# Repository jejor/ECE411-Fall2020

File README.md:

# ECE411-Fall2020
Practicum Project: Safety Bar
Tiffani Shilts Hartman <tshilts2@pdx.edu>, Jennifer Jordan <jejor2@pdx.edu>, Katie Loseke <kloseke@pdx.edu>, Seth Rohrbach <rseth@pdx.edu>

## Executive Summary / Concept of Operations

This is a LED light bar system which will display power information from a distance of 300 feet. This system will be installed on a liquid fuel engine test stand and will display which sub-systems are receiving power and will display data on which individual valves are receiving power during the different engine firing stages. 

## Brief Market Analysis

This project can be adapted for a system with up to 9 inputs to display the power states of the lines. This is a safety and data sub-system for ensuring that all lines are powered as they should be within the purposes of the whole system. The Safety Bar would cost less than $200 if brought to market; this includes a rough estimate of component cost and assembly.

## Requirements

- Must be visible from 300 feet (91.5 meters).
- Must be able to take at least 9 power line (valve) inputs.
- Must be compatible with a 24V input to power the system.
- Should display all possible combinations of power states.
- Should cost less than $200 total.
- Should compare State Machine to the current valve states.
- Should have a battery backup with 1 hour of backup power.
- Should be protected from the elements within an enclosure.
- Should have thermal distribution system.
- May have data backup on the micro-controller.
- May be enclosed in an explosion proof box.
- May have rechargeable battery.

## System Architecture

#### The full system architecture for the Test Stand Automation & Regulation system with the Safety Bar sub-project (green circle):

#### Safety Bar Level 0 Block Diagram:

#### Safety Bar Level 1 Block Diagram:

## Design Specification

There are a total of 9 valves which states need to be compared to the software control state machine. This system will verify that the valves are responding to the software commands. To do this we will use sensors on each 9 valves, process the data on a micro-controller, compare the physical valve states to the expected valve states and display any relevant information to the user in the form of LED display codes. The LED bar will display the current state the system is in, if there is an error or if the physical state does not match the expected state, the LED bar will flash and display which valve is causing the error. 

- Sensor: Hall Effect
- Processor: STM32F0
- Actuator: LEDs
- Power: POE+ with backup battery

`Software Pseudocode:`

`LOOP:`

&nbsp;&nbsp;&nbsp;&nbsp; `READ: hall effect sensors`

&nbsp;&nbsp;&nbsp;&nbsp; `READ: STM32F0 state command`

&nbsp;&nbsp;&nbsp;&nbsp; `COMPARE: hall effect sensor data to state command`

&nbsp;&nbsp;&nbsp;&nbsp;&nbsp;&nbsp;&nbsp;&nbsp; `IF: doesn’t match`

&nbsp;&nbsp;&nbsp;&nbsp;&nbsp;&nbsp;&nbsp;&nbsp;&nbsp;&nbsp;&nbsp;&nbsp; `Sound Buzzer`

&nbsp;&nbsp;&nbsp;&nbsp;&nbsp;&nbsp;&nbsp;&nbsp;&nbsp;&nbsp;&nbsp;&nbsp; `Display binary value for which valve is causing the error`

&nbsp;&nbsp;&nbsp;&nbsp;&nbsp;&nbsp;&nbsp;&nbsp; `IF: does match`

&nbsp;&nbsp;&nbsp;&nbsp;&nbsp;&nbsp;&nbsp;&nbsp;&nbsp;&nbsp;&nbsp;&nbsp; `Display current state in binary`

&nbsp;&nbsp;&nbsp;&nbsp; `RECORD: data to SD card`

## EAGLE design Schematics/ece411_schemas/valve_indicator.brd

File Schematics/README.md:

# Eagle Schematics & Boards

## Valve Indicator

Purpose:
This board will collect valve position data using hall effect sensors mounted on nine solenoid valves and will report the current commanded state of the valves. 
The processor will compare the expected valve states with the currect reported valve states, 
if the states do not match the processor will output an indication over the LED arrays.
The LED arrays will display specific binary codes to indicate which valve does not match. 
If multiple valves do not match then the LED arrays will display all binary codes one after another based upon priority information.

Inputs:
- POE+ 24V Power
- UART Data
- Nine Hall Effect Sensors
- ST-Link V2 Emulator

Processor:
- STM32F042K

Outputs:
- Three LED Arrays
- One Buzzer
- SD Card Data Backup

### Libraries In Use

- Power Regulators: Diodes Inc. - AZ34063UMTR-G1.lbr
- Test Points: oresat-misc.lbr
- Processor: U-ST-STM32F042K-uC.lbr
- JTAG Emulator Connector: J-Samtec-FTSH-105-XXX-DV-K-ARM-SWD.lbr
- Diode: On Semiconductor - 1N5819G.lbr

### Design Rules

We are using the OshPark design rules for a 2-layer board.

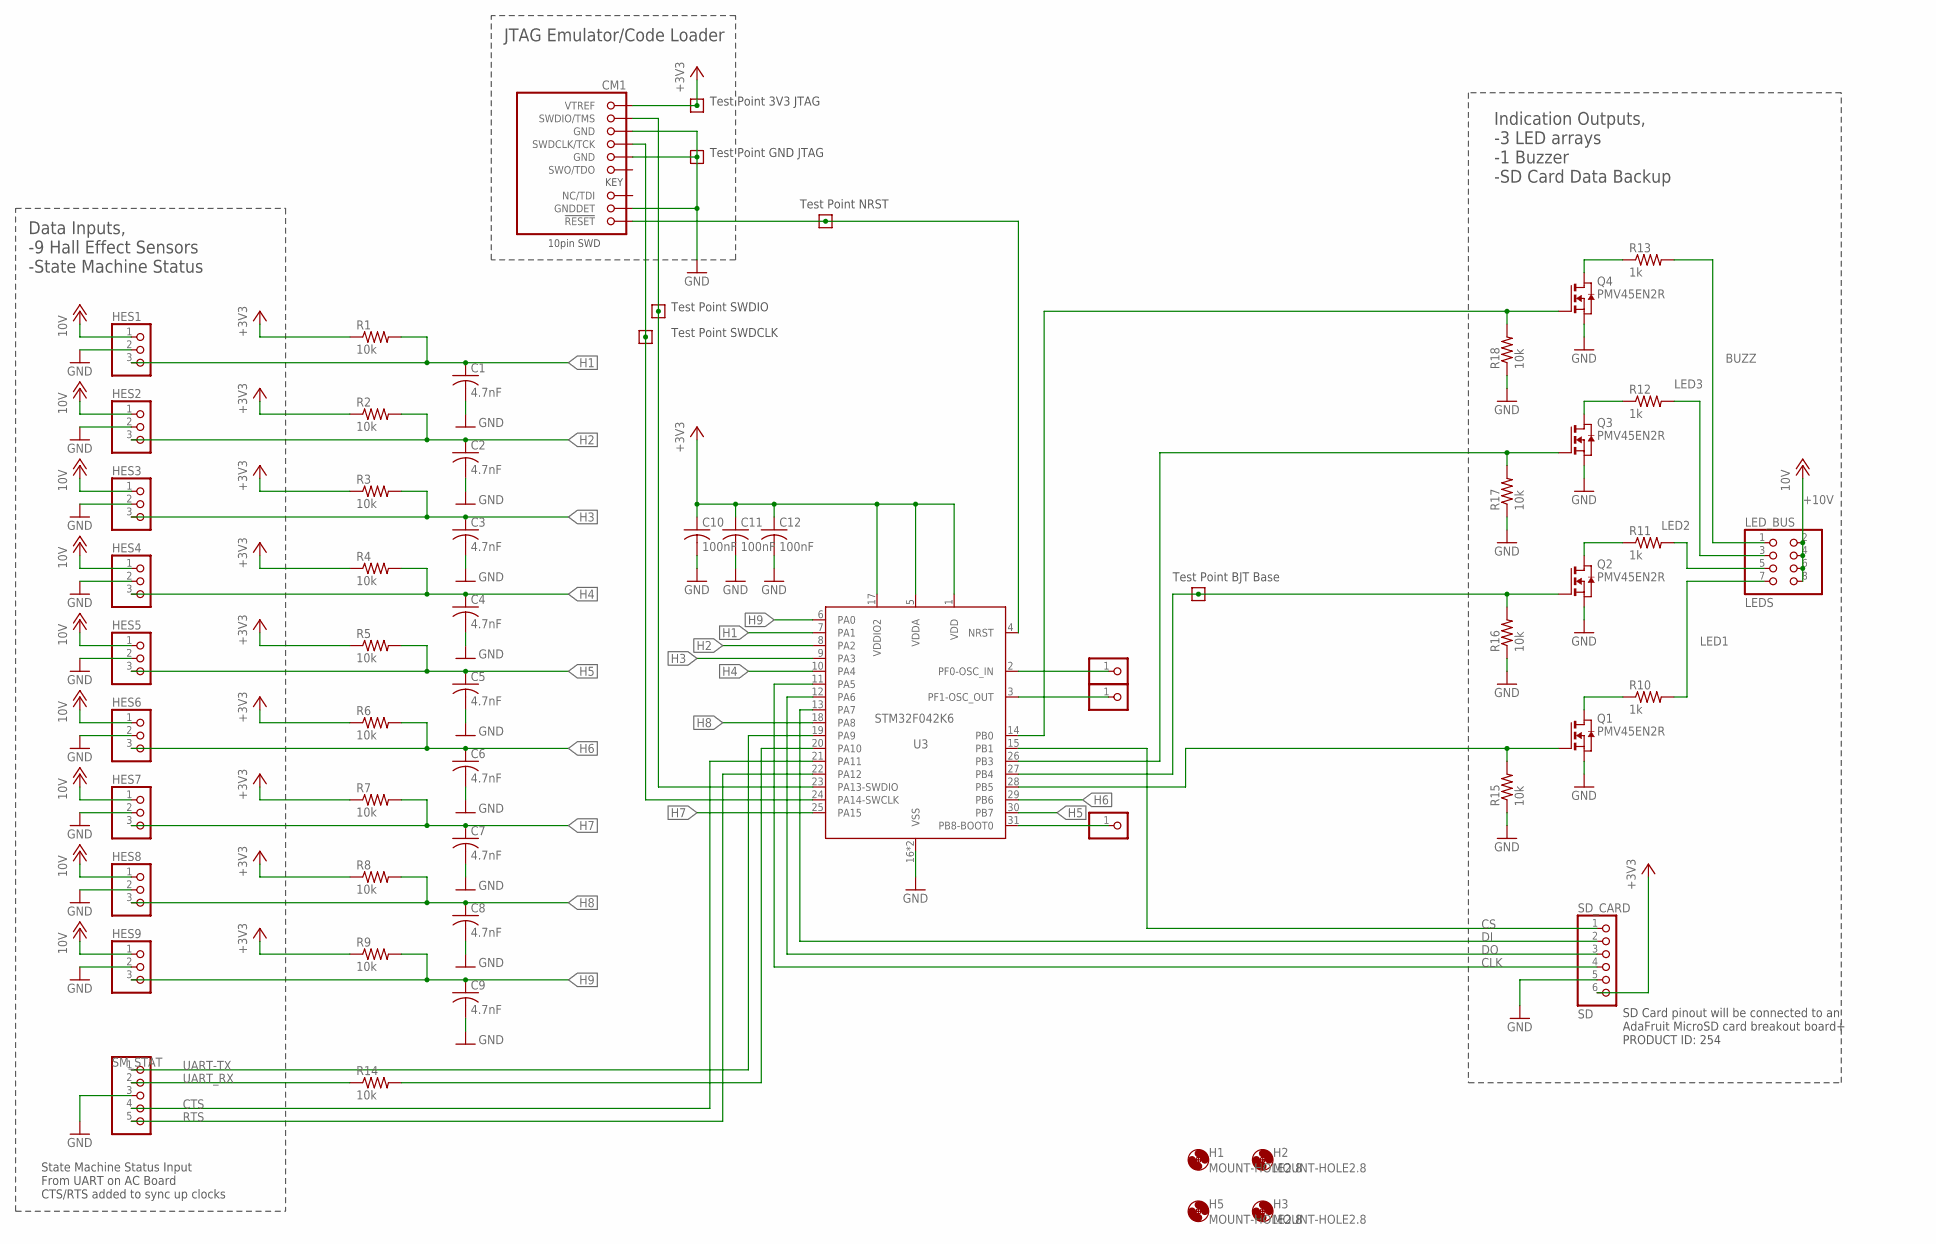
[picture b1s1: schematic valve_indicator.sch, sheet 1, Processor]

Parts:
C1, C2, C3, C4, C5, C6, C7, C8, C9: 4.7nF; C0603; MPN C1608C0G1H472J080AA
C10, C11, C12: 100nF; C0603; MPN CL10B104KA8NNNC
CM1: FTSH-105-XX-X-DV-K; CON10_2X5_DUK_FTSH; MPN FTSH-105-01-F-DV-K-TR
H1, H2, H3, H5: MOUNT-HOLE2.8; 2,8
HES1: HES1; 1X03; MPN 0022112032
HES2: HES2; 1X03; MPN 0022112032
HES3: HES3; 1X03; MPN 0022112032
HES4: HES4; 1X03; MPN 0022112032
HES5: HES5; 1X03; MPN 0022112032
HES6: HES6; 1X03; MPN 0022112032
HES7: HES7; 1X03; MPN 0022112032
HES8: HES8; 1X03; MPN 0022112032
HES9: HES9; 1X03; MPN 0022112032
JP2: PF0-OSC_IN_PIN; 1X01
JP3: PF1-OSC_OUT_PIN; 1X01
JP4: PB8-BOOT0_PIN; 1X01
LED_BUS: LEDS; 2X04
Q1, Q2, Q3, Q4: PMV45EN2R; SOT23; MPN PMV45EN2R
R1, R2, R3, R4, R5, R6, R7, R8, R9, R14, R15, R16, R17, R18: 10k; R0603; MPN RMCF0603FT10K0
R10, R11, R12, R13: 1k; R0603; MPN RMCF0603JJ1K00
SD_CARD: SD; 1X06; MPN 5-103635-5
SM_STAT: SM_STAT; 1X05; MPN 0022112032
TP3V3J: TEST-POINT-LARGE-SQUARE; 1X01
TPBASE: TEST-POINT-LARGE-SQUARE; 1X01
TPJGND: TEST-POINT-LARGE-SQUARE; 1X01
TPNRST: TEST-POINT-LARGE-SQUARE; 1X01
TPSCLK: TEST-POINT-LARGE-SQUARE; 1X01
TPSIO: TEST-POINT-LARGE-SQUARE; 1X01
U3: STM32F042K6; QFP32-7X7; MPN STM32F042K6T6

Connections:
+3V3: C10.1, C11.1, C12.1, CM1.1 (VTREF), R1.1, R2.1, R3.1, R4.1, R5.1, R6.1, R7.1, R8.1, R9.1, SD_CARD.6, TP3V3J.1, U3.1 (VDD), U3.5 (VDDA), U3.17 (VDDIO2); also elsewhere on the board
+10V: HES1.1, HES2.1, HES3.1, HES4.1, HES5.1, HES6.1, HES7.1, HES8.1, HES9.1, LED_BUS.2, LED_BUS.4, LED_BUS.6, LED_BUS.8; also elsewhere on the board
BUZZ: LED_BUS.1, R13.2
CLK: SD_CARD.4, U3.11 (PA5)
CS: SD_CARD.1, U3.15 (PB1)
CTS: SM_STAT.4, U3.21 (PA11)
DI: SD_CARD.2, U3.13 (PA7)
DO: SD_CARD.3, U3.12 (PA6)
GND: C1.2, C2.2, C3.2, C4.2, C5.2, C6.2, C7.2, C8.2, C9.2, C10.2, C11.2, C12.2, CM1.3 (GND), CM1.5 (GND), CM1.9 (GNDDET), HES1.2, HES2.2, HES3.2, HES4.2, HES5.2, HES6.2, HES7.2, HES8.2, HES9.2, Q1.2 (S), Q2.2 (S), Q3.2 (S), Q4.2 (S), R15.1, R16.1, R17.1, R18.1, SD_CARD.5, SM_STAT.3, TPJGND.1, U3.16 (VSS), U3.32 (VSS); also elsewhere on the board
H1: C1.1, HES1.3, R1.2, U3.7 (PA1)
H2: C2.1, HES2.3, R2.2, U3.8 (PA2)
H3: C3.1, HES3.3, R3.2, U3.9 (PA3)
H4: C4.1, HES4.3, R4.2, U3.10 (PA4)
H5: C5.1, HES5.3, R5.2, U3.30 (PB7)
H6: C6.1, HES6.3, R6.2, U3.29 (PB6)
H7: C7.1, HES7.3, R7.2, U3.25 (PA15)
H8: C8.1, HES8.3, R8.2, U3.18 (PA8)
H9: C9.1, HES9.3, R9.2, U3.6 (PA0)
LED1: LED_BUS.7, R10.2
LED2: LED_BUS.5, R11.2
LED3: LED_BUS.3, R12.2
unnamed: Q4.3 (D), R13.1
unnamed: JP2.1, U3.2 (PF0-OSC_IN)
unnamed: JP3.1, U3.3 (PF1-OSC_OUT)
unnamed: JP4.1, U3.31 (PB8-BOOT0)
unnamed: CM1.4 (SWDCLK/TCK), TPSCLK.1, U3.24 (PA14-SWCLK)
unnamed: Q3.3 (D), R12.1
unnamed: Q1.1 (G), R15.2, U3.28 (PB5)
unnamed: Q3.1 (G), R17.2, U3.26 (PB3)
unnamed: Q1.3 (D), R10.1
unnamed: Q2.3 (D), R11.1
unnamed: CM1.2 (SWDIO/TMS), TPSIO.1, U3.23 (PA13-SWDIO)
unnamed: CM1.10 (!RESET), TPNRST.1, U3.4 (NRST)
unnamed: Q4.1 (G), R18.2, U3.14 (PB0)
unnamed: Q2.1 (G), R16.2, TPBASE.1, U3.27 (PB4)
RTS: SM_STAT.5, U3.22 (PA12)
UART-RX: R14.2, U3.20 (PA10)
UART-TX: SM_STAT.1, U3.19 (PA9)
UART_RX: R14.1, SM_STAT.2

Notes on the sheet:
State Machine Status Input From UART on AC Board CTS/RTS added to sync up clocks
Data Inputs, -9 Hall Effect Sensors -State Machine Status
Indication Outputs, -3 LED arrays -1 Buzzer -SD Card Data Backup
JTAG Emulator/Code Loader
Test Point 3V3 JTAG
Test Point GND JTAG
Test Point NRST
Test Point SWDCLK
Test Point SWDIO
Test Point BJT Base
SD Card pinout will be connected to an AdaFruit MicroSD card breakout board+ PRODUCT ID: 254

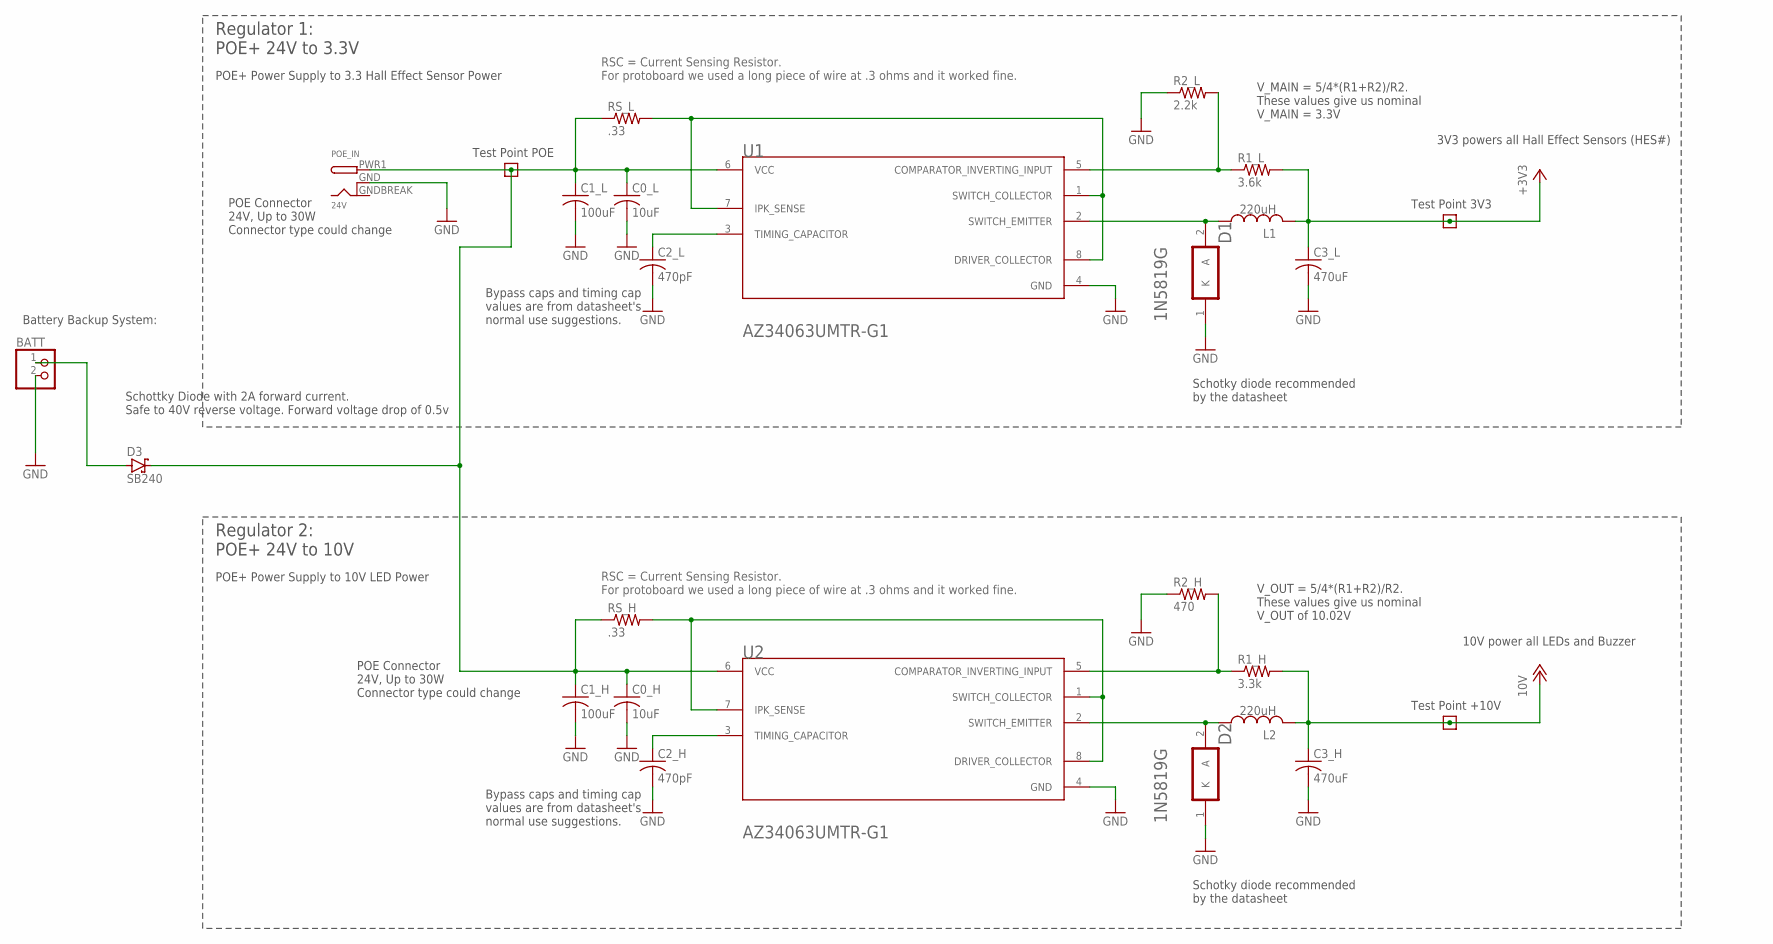
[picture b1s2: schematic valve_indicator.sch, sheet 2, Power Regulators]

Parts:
BATT: LED1; 1X02; MPN 0022232021
C0_H, C0_L: 10uF; C1206; MPN CL31A106MBHNNNE
C1_H, C1_L: 100uF; C025-025X050; MPN 107CKR050M
C2_H, C2_L: 470pF; C0603; MPN 0603B471K500CT
C3_H, C3_L: 470uF; C025-025X050; MPN ESH477M050AH4AA
D1, D2: 1N5819G_0_0; ON_SEMICONDUCTOR_1N5819G_0
D3: SB240; DO41-7.6; MPN SB240-E3/54
L1, L2: 220uH; 0204/5; MPN 12RS224C
POE_IN: 24V; DCJACK_2MM_SMT
R1_H: 3.3k; R0603; MPN RC0603FR-073K3L
R1_L: 3.6k; R0603; MPN RC0603FR-073K6L
R2_H: 470; R0603; MPN CRGCQ0603F470R
R2_L: 2.2k; R0603; MPN ERJ-3EKF2201V
RS_H: .33; R0603; MPN ERJ-3RQFR33V
RS_L: .33; R0603; MPN ERJ-3RQFR33V
TP3V3, TP10V: TEST-POINT-LARGE-SQUARE; 1X01
TPOE: TEST-POINT-LARGE-SQUARE; 1X01
U1, U2: AZ34063UMTR-G1; DIODES_INC._AZ34063UMTR-G1_0

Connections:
+3V3: C3_L.1, L1.2, R1_L.2, TP3V3.1; also elsewhere on the board
+10V: C3_H.1, L2.2, R1_H.2, TP10V.1; also elsewhere on the board
GND: BATT.2, C0_H.2, C0_L.2, C1_H.2, C1_L.2, C2_H.2, C2_L.2, C3_H.2, C3_L.2, D1.1 (K), D2.1 (K), POE_IN.GND (GNDBREAK), POE_IN.GNDBREAK (GND), R2_H.1, R2_L.1, U1.4 (GND), U2.4 (GND); also elsewhere on the board
unnamed: RS_L.2, U1.1 (SWITCH_COLLECTOR), U1.7 (IPK_SENSE), U1.8 (DRIVER_COLLECTOR)
unnamed: C2_L.1, U1.3 (TIMING_CAPACITOR)
unnamed: R1_L.1, R2_L.2, U1.5 (COMPARATOR_INVERTING_INPUT)
unnamed: D1.2 (A), L1.1, U1.2 (SWITCH_EMITTER)
unnamed: BATT.1, D3.A
unnamed: RS_H.2, U2.1 (SWITCH_COLLECTOR), U2.7 (IPK_SENSE), U2.8 (DRIVER_COLLECTOR)
unnamed: C2_H.1, U2.3 (TIMING_CAPACITOR)
unnamed: R1_H.1, R2_H.2, U2.5 (COMPARATOR_INVERTING_INPUT)
unnamed: D2.2 (A), L2.1, U2.2 (SWITCH_EMITTER)
POE: C0_H.1, C0_L.1, C1_H.1, C1_L.1, D3.C, POE_IN.PWR1 (PWR), RS_H.1, RS_L.1, TPOE.1, U1.6 (VCC), U2.6 (VCC)

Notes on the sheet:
POE Connector 24V, Up to 30W Connector type could change
Bypass caps and timing cap values are from datasheet's normal use suggestions.
V_MAIN = 5/4*(R1+R2)/R2. These values give us nominal V_MAIN = 3.3V
Schotky diode recommended by the datasheet
Regulator 1: POE+ 24V to 3.3V
3V3 powers all Hall Effect Sensors (HES#)
POE+ Power Supply to 3.3 Hall Effect Sensor Power
V_OUT = 5/4*(R1+R2)/R2. These values give us nominal V_OUT of 10.02V
Regulator 2: POE+ 24V to 10V
10V power all LEDs and Buzzer
POE+ Power Supply to 10V LED Power
Battery Backup System:
Schottky Diode with 2A forward current. Safe to 40V reverse voltage. Forward voltage drop of 0.5v
Test Point 3V3
Test Point +10V
Test Point POE
RSC = Current Sensing Resistor. For protoboard we used a long piece of wire at .3 ohms and it worked fine.

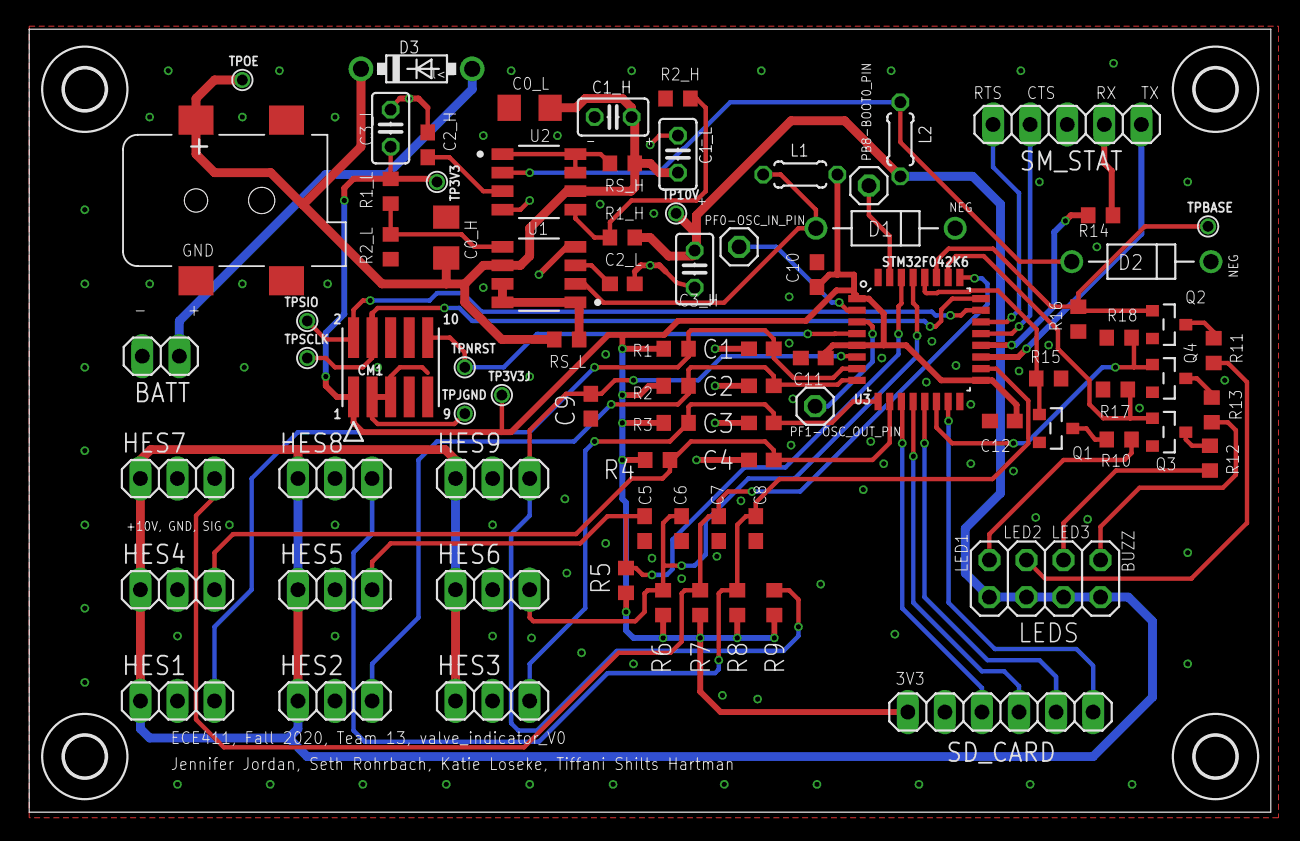
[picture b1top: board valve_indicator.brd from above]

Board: 2 copper layers, 85.1 x 53.6 mm, 87 parts (0 on the bottom side), 49 nets.

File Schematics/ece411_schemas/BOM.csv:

"Qty";"Value";"Device";"Package";"Parts";"Description";"DIS";"DPN";"MFR";"MPN";"POPULARITY";"SPICEPREFIX";
"2";".33";"R-US_R0603";"R0603";"RS_H, RS_L";"RESISTOR, American symbol";"Digi-Key";"P.33AJCT-ND";"Panasonic Electronic Components";"ERJ-3RQFR33V";"77";"R";
"3";"100nF";"C-USC0603";"C0603";"C10, C11, C12";"CAPACITOR, American symbol";"Digi-Key";"1276-1006-1-ND";" Samsung Electro-Mechanics";"CL10B104KA8NNNC";"37";"C";
"2";"100uF";"C-US025-025X050";"C025-025X050";"C1_H, C1_L";"CAPACITOR, American symbol";"Digi-Key";"1572-1044-ND";"Illinois Capacitor";"107CKR050M";"0";"C";
"9";"10k";"R-US_R0603";"R0603";"R1, R2, R3, R4, R5, R6, R7, R8, R9";"RESISTOR, American symbol";"Digi-Key";"RMCF0603FT10K0CT-ND";"Stackpole Electronics Inc";"RMCF0603FT10K0";"77";"R";
"2";"10uF";"C-USC1206";"C1206";"C0_H, C0_L";"CAPACITOR, American symbol";"Digi-Key";"1276-6736-1-ND";"Samsung Electro-Mechanics";"CL31A106MBHNNNE";"24";"C";
"2";"1N5819G_0_0";"ON_SEMICONDUCTOR_1N5819GON_SEMICONDUCTOR_1N5819G_0_0";"ON_SEMICONDUCTOR_1N5819G_0";"D1, D2";"ONSC-D-K1A2-2_A";"Digi-Key";"1N5819GOS-ND";"On Semiconductor";"1N5819G";"";"";
"1";"2.2k";"R-US_R0603";"R0603";"R2_L";"RESISTOR, American symbol";"Digi-Key";"P2.20KHCT-ND";"Panasonic Electronic Components";"ERJ-3EKF2201V";"77";"R";
"2";"220uH";"L-US0204/5";"0204/5";"L1, L2";"INDUCTOR, American symbol";"Mouser";"994-RFS1317-224KL";"Coilcraft";"RFS1317-224KL";"0";"L";
"1";"24V";"DCBARRELSMT";"DCJACK_2MM_SMT";"POE_IN";"2.0mm DC Barrel Jack";"";"";"";"";"";"";
"4";"2N2222";"-NPN-SOT23-EBC";"SOT23-EBC";"T1, T2, T3, T4";"NPN Transistror";"Digi-Key";"1727-2956-1-ND";"Nexperia USA Inc.";"PMBT2222A,215";"0";"";
"1";"3.3k";"R-US_R0603";"R0603";"R1_H";"RESISTOR, American symbol";"Digi-Key";"311-3.30KHRCT-ND";"Yageo";"RC0603FR-073K3L";"77";"R";
"1";"3.6k";"R-US_R0603";"R0603";"R1_L";"RESISTOR, American symbol";"Digi-Key";"311-3.60KHRCT-ND";"Yageo";"RC0603FR-073K6L";"77";"R";
"9";"4.7nF";"C-USC0603";"C0603";"C1, C2, C3, C4, C5, C6, C7, C8, C9";"CAPACITOR, American symbol";"Digi-Key";"445-7400-1-ND";"TDK Corporation";"C1608C0G1H472J080AA";"37";"C";
"1";"470";"R-US_R0603";"R0603";"R2_H";"RESISTOR, American symbol";"Digi-Key";"A129684CT-ND";"TE Connectivity Passive Product";"CRGCQ0603F470R";"77";"R";
"2";"470pF";"C-USC0603";"C0603";"C2_H, C2_L";"CAPACITOR, American symbol";"Digi-Key";"1292-1438-1-ND";"Walsin Technology Corporation";"0603B471K500CT";"37";"C";
"2";"470uF";"C-USC0603";"C0603";"C3_H, C3_L";"CAPACITOR, American symbol";"Digi-Key";"399-15683-ND";"KEMET";"ESH477M050AH4AA";"37";"C";
"2";"AZ34063UMTR-G1";"DIODES_INC._AZ34063UMTR-G1DIODES_INC._AZ34063UMTR-G1_0_0";"DIODES_INC._AZ34063UMTR-G1_0";"U1, U2";"Buck, Boost Switching Regulator IC Positive or Negative Adjustable 1.25V 1 Output 1.5A (Switch) 8-SOIC (0.154", 3.90mm Width)";"Digi-Key";"AZ34063UMTR-G1DICT-ND";"Diodes Incorporated";"AZ34063UMTR-G1";"";"";
"1";"BUZZER";"PINHD-1X2";"1X02";"BUZZER";"PIN HEADER";"";"";"";"";"98";"";
"1";"FTSH-105-XX-X-DV-K";"FTSH-105-XX-X-DV-K";"CON10_2X5_DUK_FTSH";"CM1";"";"Digi-Key";"SAM13160CT-ND";"Samtec Inc.";"FTSH-105-01-F-DV-K-TR";"";"";
"1";"HES1";"PINHD-1X3";"1X03";"HES1";"PIN HEADER";"";"";"";"";"92";"";
"1";"HES2";"PINHD-1X3";"1X03";"HES2";"PIN HEADER";"";"";"";"";"92";"";
"1";"HES3";"PINHD-1X3";"1X03";"HES3";"PIN HEADER";"";"";"";"";"92";"";
"1";"HES4";"PINHD-1X3";"1X03";"HES4";"PIN HEADER";"";"";"";"";"92";"";
"1";"HES5";"PINHD-1X3";"1X03";"HES5";"PIN HEADER";"";"";"";"";"92";"";
"1";"HES6";"PINHD-1X3";"1X03";"HES6";"PIN HEADER";"";"";"";"";"92";"";
"1";"HES7";"PINHD-1X3";"1X03";"HES7";"PIN HEADER";"";"";"";"";"92";"";
"1";"HES8";"PINHD-1X3";"1X03";"HES8";"PIN HEADER";"";"";"";"";"92";"";
"1";"HES9";"PINHD-1X3";"1X03";"HES9";"PIN HEADER";"";"";"";"";"92";"";
"2";"LED1";"PINHD-1X2";"1X02";"BATT, LED1";"PIN HEADER";"";"";"";"";"98";"";
"1";"LED2";"PINHD-1X2";"1X02";"LED2";"PIN HEADER";"";"";"";"";"98";"";
"1";"LED3";"PINHD-1X2";"1X02";"LED3";"PIN HEADER";"";"";"";"";"98";"";
"4";"MOUNT-HOLE2.8";"MOUNT-HOLE2.8";"2,8";"H1, H2, H3, H5";"MOUNTING HOLE with drill center marker";"";"";"";"";"15";"";
"4";"NP";"R-US_R0603";"R0603";"R10, R11, R12, R13";"RESISTOR, American symbol";"";"";"";"";"77";"R";
"1";"SB240";"1N5817-B";"DO41-7.6";"D3";"1.0A SCHOTTKY BARRIER RECTIFIER";"Digi-Key";"SB240-E3/54GICT-ND";"Vishay Semiconductor Diodes Division";"SB240-E3/54";"0";"";
"1";"SD_CARD";"PINHD-1X8";"1X08";"SD_CARD";"PIN HEADER";"";"";"";"";"67";"";
"1";"SM_STAT";"PINHD-1X2";"1X02";"SM_STAT";"PIN HEADER";"";"";"";"";"98";"";
"1";"STM32F042K6";"STM32F042K6";"QFP32-7X7";"U3";"";"";"";"";"";"";"";
"9";"TEST-POINT-LARGE-SQUARE";"TEST-POINT-LARGE-SQUARE";"1X01";"TP3V3, TP3V3J, TP10V, TPBASE, TPJGND, TPNRST, TPOE, TPSCLK, TPSIO";"";"";"";"";"";"";"";

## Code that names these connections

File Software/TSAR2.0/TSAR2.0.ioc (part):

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Mcu.Name=STM32F042K(4-6)Ux
Mcu.Package=UFQFPN32
Mcu.UserName=STM32F042K6Ux
PA0.GPIOParameters=GPIO_PuPd,GPIO_Label
PA0.GPIO_Label=Hall Effect Sensor Nine
PA0.GPIO_PuPd=GPIO_PULLUP
PA0.Signal=GPIO_Input
PA1.GPIOParameters=GPIO_PuPd,GPIO_Label
PA1.GPIO_Label=Hall Effect Sensor One
PA1.GPIO_PuPd=GPIO_PULLUP
PA1.Signal=GPIO_Input
PA10.Mode=Asynchronous
PA10.Signal=USART1_RX
PA11.Mode=CTS_RTS
PA11.Signal=USART1_CTS
PA12.Mode=CTS_RTS
PA12.Signal=USART1_RTS
PA15.GPIOParameters=GPIO_PuPd,GPIO_Label
PA15.GPIO_Label=Hall Effect Sensor Seven
PA15.GPIO_PuPd=GPIO_PULLUP
PA15.Signal=GPIO_Input
PA2.GPIOParameters=GPIO_PuPd,GPIO_Label
PA2.GPIO_Label=Hall Effect Sensor Two
PA2.GPIO_PuPd=GPIO_PULLUP
PA2.Signal=GPIO_Input
PA3.GPIOParameters=GPIO_PuPd,GPIO_Label
PA3.GPIO_Label=Hall Effect Sensor Three
PA3.GPIO_PuPd=GPIO_PULLUP
PA3.Signal=GPIO_Input
PA4.GPIOParameters=GPIO_PuPd,GPIO_Label
PA4.GPIO_Label=Hall Effect Sensor Four
PA4.GPIO_PuPd=GPIO_PULLUP
PA4.Signal=GPIO_Input
PA5.Mode=Full_Duplex_Master
PA5.Signal=SPI1_SCK
PA6.Mode=Full_Duplex_Master
PA6.Signal=SPI1_MISO
PA7.Mode=Full_Duplex_Master
PA7.Signal=SPI1_MOSI
PA8.GPIOParameters=GPIO_PuPd,GPIO_Label
PA8.GPIO_Label=Hall Effect Sensor Eight
PA8.GPIO_PuPd=GPIO_PULLUP
PA8.Signal=GPIO_Input
PA9.Mode=Asynchronous
PA9.Signal=USART1_TX
PB0.GPIOParameters=PinState,GPIO_PuPd,GPIO_Label,GPIO_ModeDefaultOutputPP
PB0.GPIO_Label=Buzzer
PB0.GPIO_ModeDefaultOutputPP=GPIO_MODE_OUTPUT_PP
PB0.GPIO_PuPd=GPIO_PULLDOWN
PB0.PinState=GPIO_PIN_SET
PB0.Signal=GPIO_Output
PB1.GPIOParameters=PinState,GPIO_Label
PB1.GPIO_Label=SD_CS
PB1.PinState=GPIO_PIN_SET
PB1.Signal=GPIO_Output
PB3.GPIOParameters=PinState,GPIO_PuPd,GPIO_Label
PB3.GPIO_Label=LED Three
PB3.GPIO_PuPd=GPIO_PULLDOWN
PB3.PinState=GPIO_PIN_SET
PB3.Signal=GPIO_Output
PB4.GPIOParameters=PinState,GPIO_PuPd,GPIO_Label
PB4.GPIO_Label=LED Two
PB4.GPIO_PuPd=GPIO_PULLDOWN
PB4.PinState=GPIO_PIN_SET
PB4.Signal=GPIO_Output
PB5.GPIOParameters=PinState,GPIO_PuPd,GPIO_Label
PB5.GPIO_Label=LED One
PB5.GPIO_PuPd=GPIO_PULLDOWN
PB5.PinState=GPIO_PIN_SET
PB5.Signal=GPIO_Output
PB6.GPIOParameters=GPIO_PuPd,GPIO_Label
PB6.GPIO_Label=Hall Effect Sensor Six
PB6.GPIO_PuPd=GPIO_PULLUP
PB6.Signal=GPIO_Input
PB7.GPIOParameters=GPIO_PuPd,GPIO_Label
PB7.GPIO_Label=Hall Effect Sensor Five
PB7.GPIO_PuPd=GPIO_PULLUP
PB7.Signal=GPIO_Input
board=custom

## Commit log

2020-10-15 PDS outline
2020-10-16 added images to readme
2020-10-16 Updated PDS
2020-10-17 Content, Format, Images
    updated PDS, fixed formatting, replaced system images
2020-10-17 411 project ideas
2020-10-17 contact info
    added emails and names
2020-10-17 trying to fix folder..
2020-10-23 Create Software
2020-10-23 Ment to be a folder
2020-10-24 -Added 1st pass for main power supply schematic
2020-10-27 Added Software Algorithm
    This is without SD card backup
2020-10-30 Not 100% sure how much of the project is needed so I'm just putting the whole project folder in
2020-10-30 moved this into the project folder
2020-10-30 combined eagle files
    combined seth's power system and processor schematic into one file with multiple sheets.
2020-10-30 swapped PTH to SMD 0603 components, fixed resistor values for 10v regulator.
    waiting on eagle library for the inductor, couldn't find an 0603 package 220 uH rated for enough current so I picked a shielded package
2020-10-31 began layout of board
    also added components attributes
2020-11-01 board layout done
2020-11-01 adding attributes to components
2020-11-01 dru added, added attributes
2020-11-02 created bom, finished attributes
2020-11-02 updated board bom
2020-11-02 added nrst pin to jtag emul
2020-11-02 added bypass caps, updated bom
    needed to add 10uF ceramic in parallel with 100uF electro caps to decrease resistance to ground
2020-11-02 added bat backup
2020-11-03 updates to board, added libraries
2020-11-04 updated board
2020-11-05 bom, layout, attribute, device
    added attributes to rest of parts
    made power lines thicker for dissapation
    editted az34.. device to remedy errors
    added test points
2020-11-06 readme for schematics/boards
2020-11-06 added state machine uart conn, labels
2020-11-06 updated inductor part
2020-11-07 added test code to make an ledblink on in PB3
2020-11-09 updated board given feedback
2020-11-09 re-doing to get around a merge conflict
2020-11-09 updated inductor attributes, some note updates on power sheet
2020-11-09 digikey --> digi-key
2020-11-10 fixed issues with board, updated BOM
2020-11-11 updated power lines
2020-11-15 initial code setup for uart and sd card
2020-11-15 datasheets for software
2020-11-16 fixed error on board
2020-11-16 added cts/rts, cleanup, added backup pins
    Added cts/rts to uart pin bus, cleaned up the schematic nets, and added pins for all the unused stm pins just in case.
2020-11-18 updated block diagrams
2020-11-18 typo
2020-11-18 fixed silkscreen
2020-11-21 Logic good, no outputs
2020-11-27 Led on logic for pushing pins
2020-11-29 corrections to board
2020-12-01 Combined software working code
2020-12-02 working (hopefully) code for sensor/LED/buzzer UNTESTED
2020-12-02 cleaner code more sd framework UNTESTED
2020-12-02 fixed silent error in line 186
2020-12-02 SD functions inserted but too large currently T.T
2020-12-03 Code for state machine and SD card compiling, not tested. Removed UART stub code for space temporarily.
2020-12-03 removed unneccessary variables
2020-12-03 fixed error
2020-12-03 removed unneccessary line
2020-12-06 turned on SWD (serial wire debug in sys config)
2020-12-07 updates to spacing on boards
